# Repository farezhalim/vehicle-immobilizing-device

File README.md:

# Vehicle Immobilizing Device
*ECE Capstone 2018-2019 Group 7*

The vehicle immobilization device monitors a vehicle's speed and acceleration through a combination of OBD-II queries and a digital accelerometer, and upon detection of a collision, the device immobilizes the vehicle by injecting CAN packets to ECUs in the vehicle. To disable the immobilization, an override is sent through Bluetooth using an Android app to the device to halt CAN message injection.

There are four main sections:
1. App (For Smartphone app for authority, disabling action)
2. Hardware (All Electrical hardware schematics, pcb's, etc. Include Mechanical Design as well, solidworks files, and concept designs.)
2. Software (Resides on main processcor, Raspberry Pi Zero W)
2. Testing  (Verification using ECU Simulator)

For more info, please view the presentation slides and report document.

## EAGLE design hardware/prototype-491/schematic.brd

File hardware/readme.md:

# Hardware design

The folders here contain hardware and conceptual designs pertaining to the project.
1. `future` contains the EAGLE schematic and board files for the design of the final product
2. `manufacturer` contains reference material used in the design (i.e. other OBD-II interpreter board)
3. `mechanical` contains the Solidworks files associated with product casing 
4. `prototype-491` contains EAGLE schematic and board files for the proof-of-concept built during ECE 491 Capstone
5. `lbr` contains all the necessary EAGLE libraries

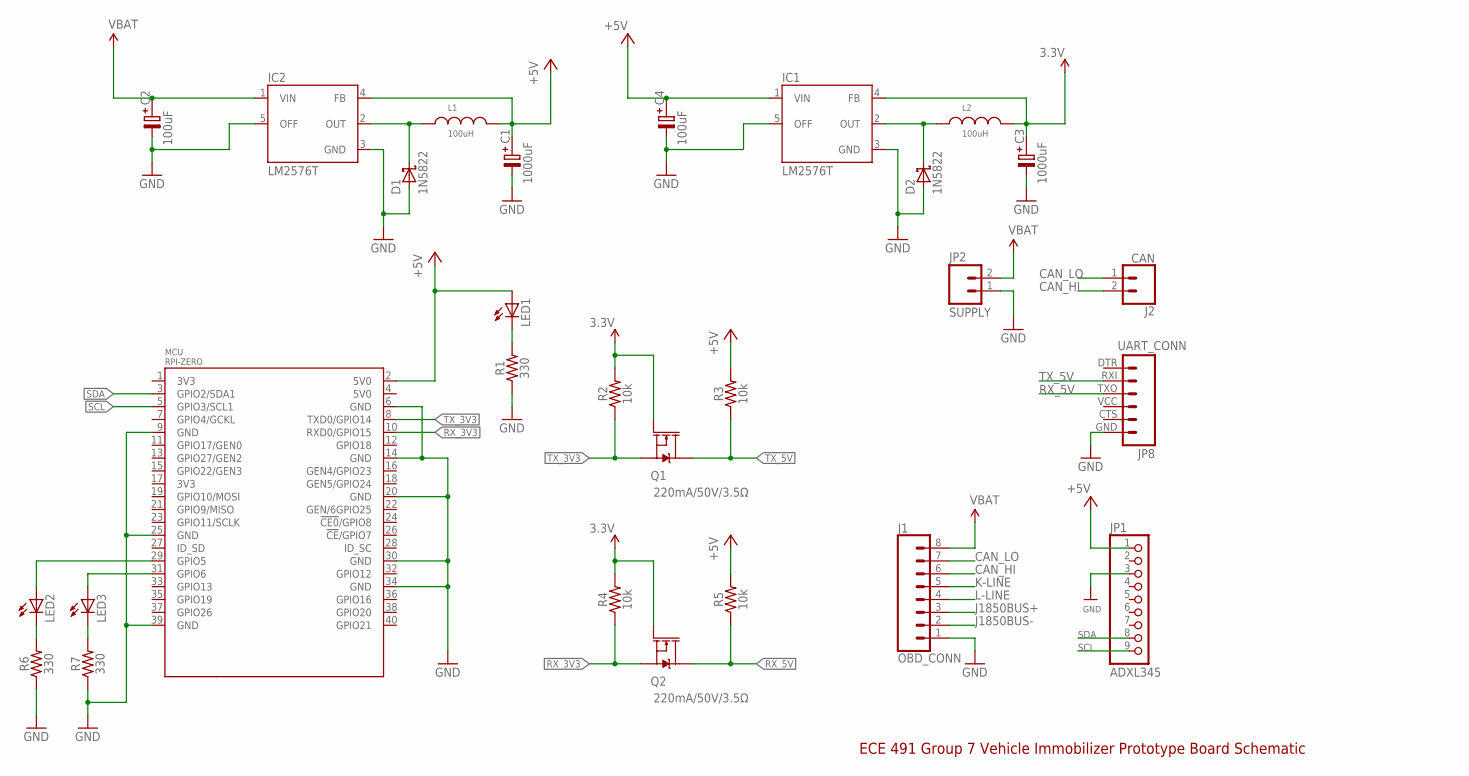
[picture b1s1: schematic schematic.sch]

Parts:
C1, C3: 1000uF; E3,5-8
C2, C4: 100uF; E3,5-8
D1, D2: 1N5822; DIOAD2120W130L950D530P
IC1, IC2: LM2576T; TO220-5
J1: OBD_CONN; 1X08
J2: CAN; MOLEX-1X2
JP1: ADXL345; 1X09_ROUND_70
JP2: SUPPLY; SCREWTERMINAL-3.5MM-2
JP8: UART_CONN; FTDI_BASIC
L1, L2: 100uH; WE-TI_1014
LED1, LED2, LED3: LED3MM
MCU: RPI-ZERO; RASPBERRYPI_BASTELSTUBE_V13_RASPI_BOARD_B+_FULL
Q1, Q2: 220mA/50V/3.5Ω; SOT23-3
R1, R6, R7: 330; AXIAL-0.3
R2, R3, R4, R5: 10k; AXIAL-0.3

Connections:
3.3V: C3.+, IC1.4 (FB), L2.2, Q1.1 (G), Q2.1 (G), R2.P$2 (2), R4.P$2 (2)
+5V: C1.+, C4.+, IC1.1 (VIN), IC2.4 (FB), JP1.1, L1.2, LED1.A, MCU.2 (5V0), R3.P$2 (2), R5.P$2 (2)
CAN_HI: J1.6, J2.2
CAN_LO: J1.7, J2.1
GND: C1.-, C2.-, C3.-, C4.-, D1.A, D2.A, IC1.3 (GND), IC1.5 (OFF), IC2.3 (GND), IC2.5 (OFF), J1.1, JP1.3, JP2.1, JP8.GND (6), MCU.6 (GND), MCU.9 (GND), MCU.14 (GND), MCU.20 (GND), MCU.25 (GND), MCU.30 (GND), MCU.34 (GND), MCU.39 (GND), R1.P$1 (1), R6.P$1 (1), R7.P$1 (1)
J1850BUS+: J1.3
J1850BUS-: J1.2
K-LINE: J1.5
L-LINE: J1.4
unnamed: D2.C, IC1.2 (OUT), L2.1
unnamed: D1.C, IC2.2 (OUT), L1.1
unnamed: LED2.K (C), R6.P$2 (2)
unnamed: LED3.K (C), R7.P$2 (2)
unnamed: LED1.K (C), R1.P$2 (2)
RX_3V3: MCU.10 (RXD0/GPIO15), Q2.2 (S), R4.P$1 (1)
RX_5V: JP8.TXO (3), Q2.3 (D), R5.P$1 (1)
SCL: JP1.9, MCU.5 (GPIO3/SCL1)
SDA: JP1.8, MCU.3 (GPIO2/SDA1)
STAT_LED1: LED2.A, MCU.29 (GPIO5)
STAT_LED2: LED3.A, MCU.31 (GPIO6)
TX_3V3: MCU.8 (TXD0/GPIO14), Q1.2 (S), R2.P$1 (1)
TX_5V: JP8.RXI (2), Q1.3 (D), R3.P$1 (1)
VBAT: C2.+, IC2.1 (VIN), J1.8, JP2.2

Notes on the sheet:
ECE 491 Group 7 Vehicle Immobilizer Prototype Board Schematic

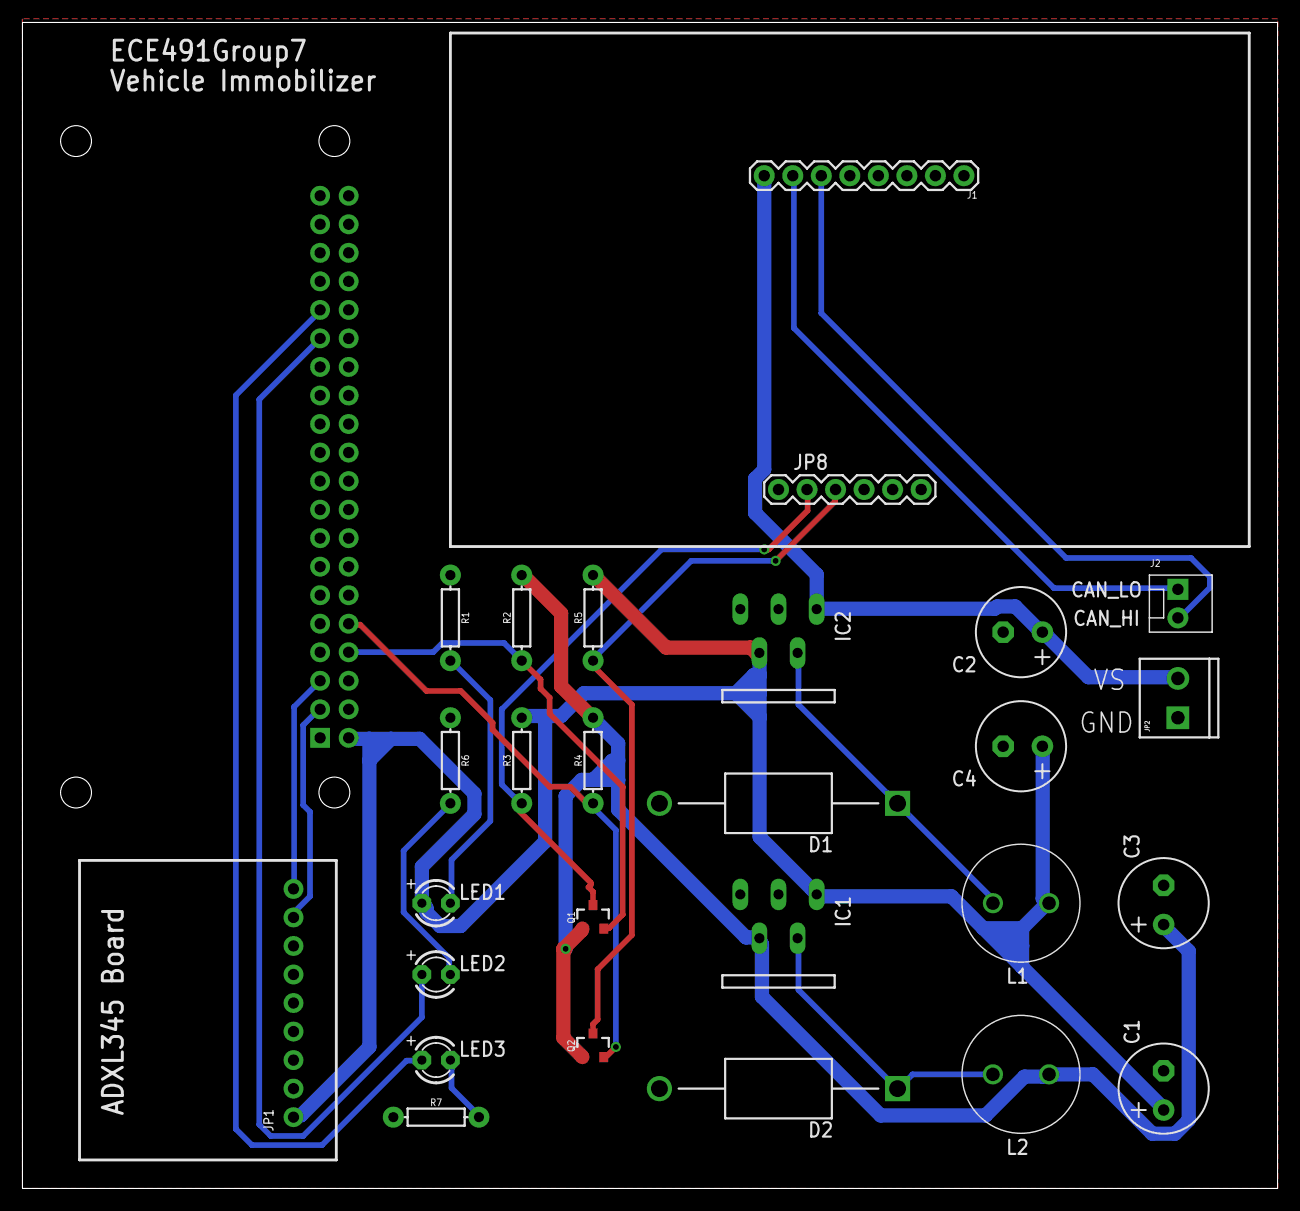
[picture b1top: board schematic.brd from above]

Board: 2 copper layers, 111.7 x 103.8 mm, 28 parts (1 on the bottom side), 19 nets.

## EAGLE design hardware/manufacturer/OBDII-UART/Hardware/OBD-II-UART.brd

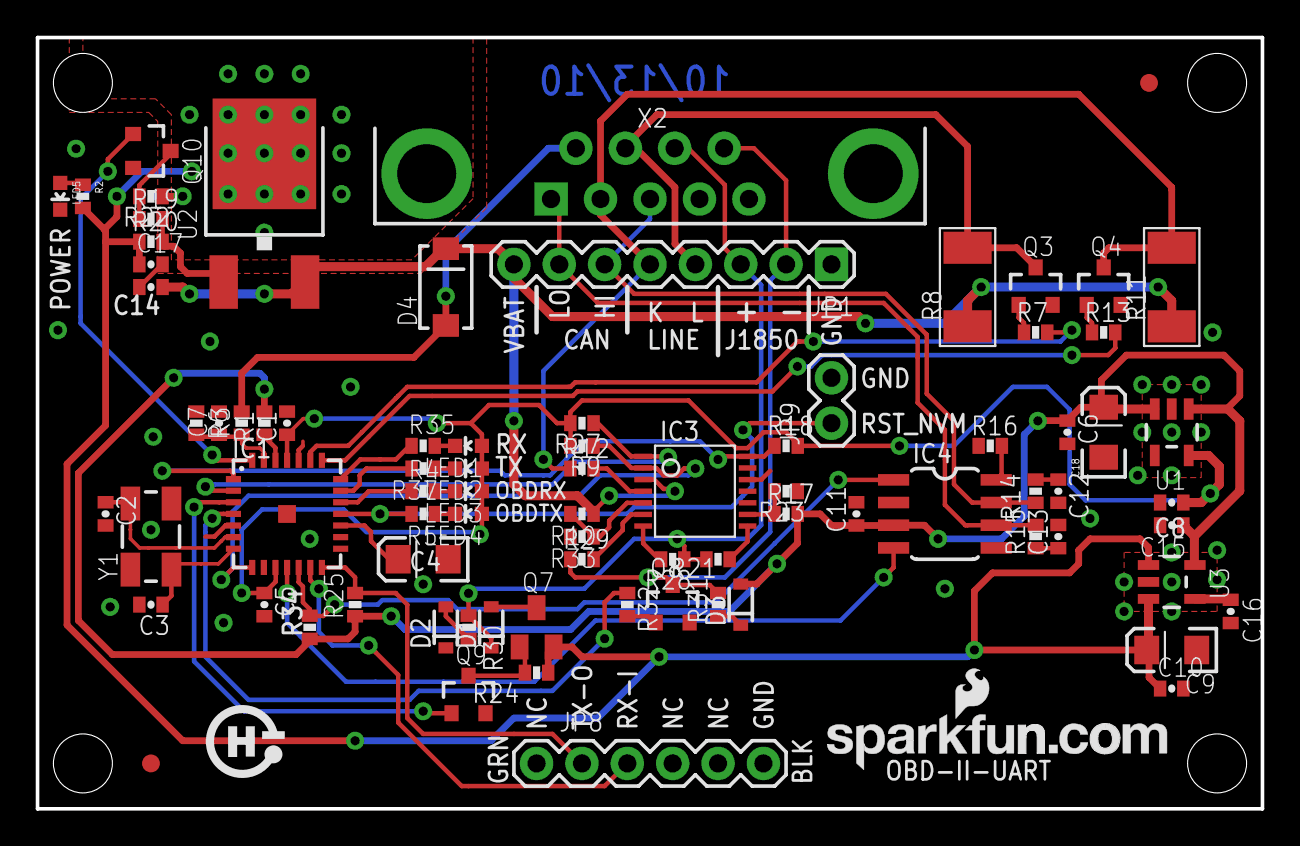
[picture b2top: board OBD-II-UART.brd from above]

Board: 2 copper layers, 68.6 x 43.2 mm, 88 parts (0 on the bottom side), 57 nets.

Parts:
C1, C5, C6, C11, C17: 1uF; 0402-CAP
C2, C3: 27pF; 0402-CAP
C4: 10uF ESR<=5; EIA3216
C7, C10, C14: 0.1uF; 0402-CAP
C8: 4.7uF; 0402-CAP
C9, C18: 10uF; EIA3216
C12, C13: 560pF; 0402-CAP
C15: 2.2uF; 0402-CAP
C16: 470pF; 0402-CAP
D1, D2, D3: BAS16; SOD-323
D4: MBRA140; SMA-DIODE
IC1: SCANTOOL; _STN_SCANTOOL_QFN-28-S
IC3: LM339PWR; TSSOP-14
IC4: MCP2551; SO-8
JP1: 1X08
JP2, JP10: FIDUCIAL1X2; FIDUCIAL-1X2
JP3: LOGO-SFENEW; SFE-NEW-WEBLOGO
JP4, JP5, JP6, JP7: STAND-OFF
JP8: DNP; FTDI_BASIC
JP9: DNP; 1X02
LED1, LED3: YELLOW; LED-0603
LED2, LED4, LED5: RED; LED-0603
Q3, Q4, Q8: MMBT2222; SOT23-3
Q7: ZXMP6A13FTA; SOT23
Q9, Q10: BSS138; SOT23-3
R1, R9, R10, R12, R18, R21, R27, R28, R29, R30, R31, R33: 10k; 0402-RES
R2, R7, R13, R32: 1k; 0402-RES
R3: 62K; 0402-RES
R4, R5, R35, R37: 330; 0402-RES
R6: 10K; 0402-RES
R8, R11: 510 0.5W; 2010
R14, R15: 100; 0402-RES
R16, R23, R25: 4.7k; 0402-RES
R17: 1.2k; 0402-RES
R19: 866; 0402-RES
R20: 240; 0402-RES
R22: 374; 0402-RES
R24, R34: 1.5k; 0402-RES
U1: 3.3V; SOT23-5
U2: V_REG_317DPACK; V-REG_DPACK
U3: 5V Reg.; SOT23-5
U$1: CREATIVE_COMMONS
U$14: OSHW-LOGO
X2: Male DB9; DB9_MALE
Y1: 16MHz; CRYSTAL-SMD-5X3

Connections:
3.3V: C1.1, C5.1, C8.1, IC1.10, IC1.25, LED1.A, LED2.A, LED3.A, LED4.A, R9.2, R18.2, R27.2, U1.5
5V: C6.1, C11.1, C15.1, C18.A, D3.2, IC4.3, R1.2, R17.2, R25.1, R34.1, U1.1, U1.3, U3.5
!ISO_K_TX: IC1.22, R13.2
!ISO_L_TX: IC1.23, R7.2
!ISO_RX: IC1.8, IC3.2, R9.1
!OBD_RX_STATUS!/PGC: IC1.19, R4.1
!VPW_RX: IC1.1, IC3.14, R18.1
BATT_V: C7.1, IC1.27, R3.1, R6.2
CAN_HI: IC4.7, JP1.6, R14.2, X2.3
CAN_LO: IC4.6, JP1.7, R15.2, X2.5
CAN_RX: IC1.11, IC4.4
CAN_TX: IC1.12, IC4.1, R34.2
GND: C1.2, C2.2, C3.2, C4.C, C5.2, C6.2, C7.2, C8.2, C9.C, C10.2, C11.2, C12.2, C13.2, C14.2, C15.2, C16.2, C17.2, C18.C, D2.1, IC1.5, IC1.16, IC1.24, IC1.EXP, IC3.12, IC4.2, JP1.1, JP8.GND, JP9.2, LED5.C, Q3.2, Q4.2, Q8.2, Q9.2, Q10.2, R6.1, R16.1, R22.1, R23.1, R33.2, U1.2, U3.2, X2.1, X2.2
J1850BUS+: D1.1, JP1.3, R21.1, R28.1, R30.1, X2.7
J1850BUS+_TX: IC1.3, Q9.1
J1850BUS-: JP1.2, Q8.3, R29.1, R31.2, X2.6
J1850BUS-_TX: IC1.4, R32.1
K-LINE: JP1.5, Q4.3, R11.2, R12.1, X2.4
L-LINE: JP1.4, Q3.3, R8.2, X2.8
unnamed: IC3.7, R28.2
unnamed: IC3.6, R29.2
unnamed: Q4.1, R13.1
unnamed: Q3.1, R7.1
unnamed: IC3.5, R10.2, R33.1
unnamed: IC3.8, R21.2
unnamed: R19.2, R20.2, U2.1
unnamed: D1.2, Q7.3
unnamed: C12.1, R14.1
unnamed: IC4.8, R16.2
unnamed: IC3.9, R17.1, R23.2
unnamed: IC3.4, R12.2
unnamed: D3.1, R31.1
unnamed: Q7.1, Q9.3, R24.2
unnamed: Q10.3, R19.1, R22.2
unnamed: D2.2, R30.2
unnamed: Q8.1, R32.2
unnamed: C4.A, IC1.17
unnamed: C13.1, R15.1
unnamed: LED3.C, R4.2
unnamed: LED4.C, R5.1
unnamed: LED5.A, R2.1
unnamed: C16.1, U3.4
unnamed: LED1.C, R35.2
unnamed: LED2.C, R37.1
OSC1: C2.1, IC1.6, Y1.3
OSC2: C3.1, IC1.7, Y1.1
PWM/!VPW: IC1.28, Q10.1
PWM_RX: IC1.2, IC3.1, R27.1
RESET: IC1.26, R1.1
RST_NVM: IC1.18, JP9.1, R5.2
RX-I: IC1.13, JP8.TXO
RX-STAT: IC1.21, R35.1
TX-O: IC1.14, JP8.RXI, R25.2
TX-STAT: IC1.20, R37.2
VBAT: C14.1, D4.C, IC3.3, JP1.8, R8.1, R10.1, R11.1, U2.3
VBATT_RAW: D4.A, R3.2, X2.9
VCC: C9.A, C10.1, C17.1, Q7.2, R2.2, R20.1, R24.1, U2.4, U3.1, U3.3

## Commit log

2018-12-19 Add new directory
2019-01-20 Adding XCode project files
2019-01-22 Firebase connected
2019-01-30 Sign in & register buttons connected to Firebase and functional
2019-01-31 MAC address querying feature works
2019-02-04 Update testing/.gitkeep Deleted emulator/.gitkeep, app_backend_db/.gitkeep files
2019-02-05 Update hardware/.gitkeep Deleted raspberry_pi/.gitkeep, accelerometer/.gitkeep files
2019-02-05 adding eagle files
2019-02-05 Updating eagle files
2019-02-05 Adding manufacturer schematics
2019-02-05 accelerometer data logger simple program
2019-02-05 prototype schematic
2019-02-05 Alert + Bluetooth Network Label
2019-02-07 schematic completed
2019-02-07 changed a connector
2019-02-07 added can bus shield libraries
2019-02-09 added git ignore
2019-02-09 routed signals
2019-02-09 Bluetooth Manager First Attempt, not tested with ZMQ
2019-02-09 Bluetooth Conf File for password
2019-02-10 added status LEDs to main board, completed board for CAN test module
2019-02-18 code to save data to csv file
2019-02-18 CAM files for PCB
2019-02-18 udpated tabs
2019-02-18 gitignore
2019-02-20 Android app files
2019-02-20 fixed sign in button
2019-02-22 all arduino / tester code
2019-02-22 r-pi immobilization module file
2019-03-09 test module updates
2019-03-10 detection.py
2019-03-10 app bluetooth functionality
2019-03-11 Added parser to git
2019-03-19 raspberry pi code
2019-03-20 android app plus updated board
2019-03-22 finalized tester module code
2019-03-22 future design schematic and layout
2019-03-30 all software working on raspberry pi 3b
2019-03-30 Verified and Tested Working Signal_Read_and_Write.ino
2019-04-06 App aesthetic fixes + future board layout
2019-04-06 App aesthetic fixes
2019-04-07 Bluetooth discover list filters out devices without a name
2019-04-12 minor schematic tweaks
2019-04-12 final report
2019-04-12 All raspberry pi code
2019-04-12 some housekeeping items
2019-04-12 housekeeping
2019-04-12 added credits in schematic
2019-04-12 added credits for bluetooth functionality code for the app
2019-04-12 Upload mainController.sh
2019-04-12 updated some comments
2019-04-12 Add readme for testing
2019-04-12 Upload New File
2019-04-12 Add new file
2019-04-12 added locking sketch
2019-04-12 Update hardware/mechanical/.gitkeep, hardware/mechanical/Solidworks_Model_-_Vision-20190412T183647Z-001.zip files Deleted hardware/Mechanical Design/.gitkeep, hardware/Mechanical Design/Solidworks_Mo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
2019-04-12 Add readme for hardware
2019-04-12 Upload locking.jpg
2019-04-12 Add app readme
2019-04-12 Deleted software/parser/.DS_Store, software/parser/Empty.txt, software/parser/Good copy.txt, software/parser/Good.txt, software/parser/Parser.py files
2019-04-12 Add accelerometer readme
2019-04-12 upload dongle.png
2019-04-12 uploaded slides in pdf format
2019-04-12 replaced edited slides with COMPLETE compressed slides

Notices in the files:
parts and their libraries:
SparkFun: Released under the Creative Commons Attribution Share-Alike 3.0 License
SparkFun: http://creativecommons.org/licenses/by-sa/3.0
cap-pan40: Copyright (C) 2004, Bob Starr
PowerMagnetics: Copyright: Würth Elektronik
